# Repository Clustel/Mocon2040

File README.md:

# Mocon
A dev boards with an upgraded LDO compared to other traditional devboards, which will allow for using devices that need higher current draw. I made this to allow for easier prototyping as it gives extra breathing space when prototyping with many components connected at once to a dev board.

# Features
	RP2040 chip
	29 GPIO pins
	12Mhz Crystal
	High current LDO

# Schematic

# PCB	

# Ordering
Upload the zipped Prod folder to JLCPCB and go through their steps for a PCBA.

# BOM if u want to solder it on your own (might be more expensive than PCBA)
| Id | Designator | Footprint | Quantity | Comment |
| --- | --- | --- | --- | --- |
| 1 | C6,C12,C3,C17,C8,C5,C4,C7,C11,C2,C9 | C_0402_1005Metric | 11 | .1uF |
| 2 | C1,C10 | C_0402_1005Metric | 2 | 1uF |
| 3 | R7,R5 | C_0402_1005Metric | 2 | 1k |
| 4 | U2 | SOT-23-5 | 1 | AP2112K-3.3 |
| 5 | C13,C14 | C_0603_1608Metric | 2 | 10uF |
| 6 | C16,C15 | C_0402_1005Metric | 2 | 33pF |
| 7 | R2,R1 | C_0402_1005Metric | 2 | 5.1k |
| 8 | J1 | USB_C_Receptacle_HRO_TYPE-C-31-M-12 | 1 | USB_C_Receptacle_USB2.0_14P |
| 9 | SW1 | SW_Push_SPST_NO_Alps_SKRK | 1 | SW_Push |
| 10 | Y1 | Crystal_SMD_3225-4Pin_3.2x2.5mm | 1 | 12 MHz |
| 11 | R3,R4 | C_0402_1005Metric | 2 | 27 |
| 12 | U1 | QFN-56-1EP_7x7mm_P0.4mm_EP3.2x3.2mm | 1 | RP2040 |
| 13 | R6 | C_0402_1005Metric | 1 | 10k |
| 14 | J4 | PinHeader_1x03_P2.54mm_Vertical | 1 | Conn_01x03 |
| 15 | U3 | Winbond_USON-8-1EP_3x2mm_P0.5mm_EP0.2x1.6mm | 1 | W25Q16JVZPIQ TR |
| 16 | J2,J3 | PinHeader_1x20_P2.54mm_Vertical | 2 | Conn_01x20 |

# Silk Screen Sneak Peeks ;)

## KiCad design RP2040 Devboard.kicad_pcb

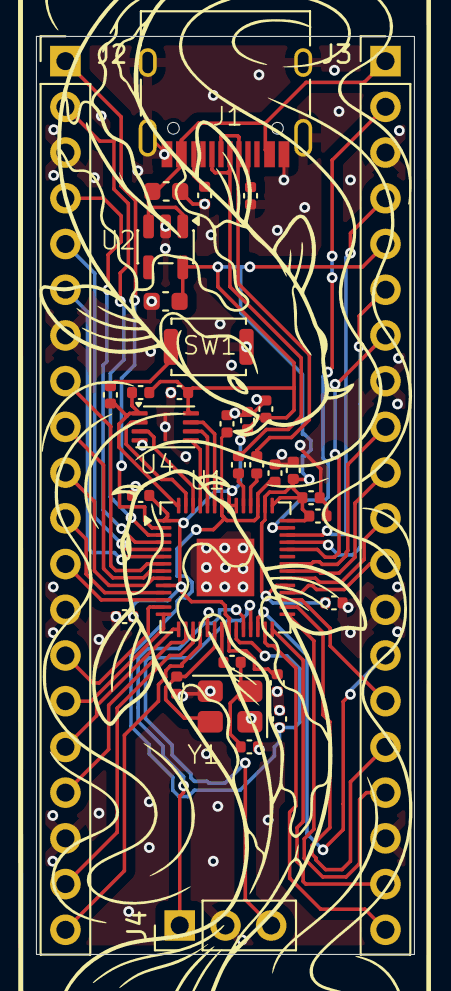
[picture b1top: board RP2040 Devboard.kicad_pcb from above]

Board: 2 copper layers, 21.0 x 51.0 mm, 33 parts (0 on the bottom side), 52 nets.

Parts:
C1, C10: 1uF; C_0402_1005Metric
C2, C3, C4, C5, C6, C7, C8, C9, C11, C12, C17: .1uF; C_0402_1005Metric
C13, C14: 10uF; C_0603_1608Metric
C15, C16: 33pF; C_0402_1005Metric
J1: USB_C_Receptacle_USB2.0_14P; USB_C_Receptacle_HRO_TYPE-C-31-M-12
J2, J3: Conn_01x20; PinHeader_1x20_P2.54mm_Vertical
J4: Conn_01x03; PinHeader_1x03_P2.54mm_Vertical
R1, R2: 5.1k; C_0402_1005Metric
R3, R4: 27; C_0402_1005Metric
R5, R7: 1k; C_0402_1005Metric
R6: 10k; C_0402_1005Metric
SW1: SW_Push; SW_Push_SPST_NO_Alps_SKRK
U1: RP2040; QFN-56-1EP_7x7mm_P0.4mm_EP3.2x3.2mm
U2: AP2112K-3.3; SOT-23-5
U3: W25Q16JVZPIQ TR; Winbond_USON-8-1EP_3x2mm_P0.5mm_EP0.2x1.6mm
Y1: 12 MHz; Crystal_SMD_3225-4Pin_3.2x2.5mm

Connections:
+1V1: C10.1, C11.1, C12.1, U1.23 (DVDD), U1.45 (VREG_VOUT), U1.50 (DVDD)
+3V3: C1.1, C2.1, C3.1, C4.1, C5.1, C6.1, C7.1, C8.1, C9.1, C13.1, C17.2, J3.5, R6.1, U1.1 (IOVDD), U1.10 (IOVDD), U1.22 (IOVDD), U1.33 (IOVDD), U1.42 (IOVDD), U1.43 (ADC_AVDD), U1.44 (VREG_VIN), U1.48 (USB_VDD), U1.49 (IOVDD), U2.5 (VOUT), U3.8 (VCC)
GND: C1.2, C2.2, C3.2, C4.2, C5.2, C6.2, C7.2, C8.2, C9.2, C10.2, C11.2, C12.2, C13.2, C14.2, C15.1, C16.1, C17.1, J1.A1 (GND), J1.A12 (GND), J1.B1 (GND), J1.B12 (GND), J1.S1 (SHIELD), J2.3, J2.7, J2.13, J2.18, J3.3, J3.8, J3.13, J3.18, J4.2, R1.2, R2.2, SW1.1, U1.19 (TESTEN), U1.57 (GND), U2.2 (GND), U3.4 (GND), U3.9 (EP), Y1.2 (G), Y1.4 (G)
GPIO0: J2.1, U1.2 (GPIO0)
GPIO1: J2.2, U1.3 (GPIO1)
GPIO2: J2.4, U1.4 (GPIO2)
GPIO3: J2.5, U1.5 (GPIO3)
GPIO4: J2.6, U1.6 (GPIO4)
GPIO5: J2.8, U1.7 (GPIO5)
GPIO6: J2.9, U1.8 (GPIO6)
GPIO7: J2.10, U1.9 (GPIO7)
GPIO8: J2.11, U1.11 (GPIO8)
GPIO9: J2.12, U1.12 (GPIO9)
GPIO10: J2.14, U1.13 (GPIO10)
GPIO11: J2.15, U1.14 (GPIO11)
GPIO12: J2.16, U1.15 (GPIO12)
GPIO13: J2.17, U1.16 (GPIO13)
GPIO14: J2.19, U1.17 (GPIO14)
GPIO15: J2.20, U1.18 (GPIO15)
GPIO16: J3.20, U1.27 (GPIO16)
GPIO17: J3.19, U1.28 (GPIO17)
GPIO18: J3.17, U1.29 (GPIO18)
GPIO19: J3.16, U1.30 (GPIO19)
GPIO20: J3.15, U1.31 (GPIO20)
GPIO21: J3.12, U1.32 (GPIO21)
GPIO22: J3.11, U1.34 (GPIO22)
GPIO23: J3.10, U1.35 (GPIO23)
GPIO24: J3.9, U1.36 (GPIO24)
GPIO26_ADC0: J3.7, U1.38 (GPIO26/ADC0)
GPIO27_ADC1: J3.6, U1.39 (GPIO27/ADC1)
GPIO28_ADC2: J3.4, U1.40 (GPIO28/ADC2)
GPIO29_ADC3: J3.2, U1.41 (GPIO29/ADC3)
unnamed: C16.2, R5.2, Y1.1
unnamed: J1.A5 (CC1), R1.1
unnamed: J1.B5 (CC2), R2.1
unnamed: R7.1, SW1.2
unnamed: R3.1, U1.46 (USB_DN)
unnamed: R4.1, U1.47 (USB_DP)
QSPI_SCLK: U1.52 (QSPI_SCLK), U3.6 (CLK)
QSPI_SD0: U1.53 (QSPI_SD0), U3.5 (DI/IO_{0})
QSPI_SD1: U1.55 (QSPI_SD1), U3.2 (DO/IO_{1})
QSPI_SD2: U1.54 (QSPI_SD2), U3.3 (~WP/IO_{2})
QSPI_SD3: U1.51 (QSPI_SD3), U3.7 (~HOLD/~RESET/IO_{3})
QSPI_SS: R6.2, R7.2, U1.56 (~QSPI_SS), U3.1 (~CS)
RUN: J3.14, U1.26 (RUN)
SWCLK: J4.1, U1.24 (SWCLK)
SWD: J4.3, U1.25 (SWDIO)
USB_DN: J1.A7 (D-), J1.B7 (D-), R3.2
USB_DP: J1.A6 (D+), J1.B6 (D+), R4.2
VBUS: C14.1, J1.A4 (VBUS), J1.A9 (VBUS), J1.B4 (VBUS), J1.B9 (VBUS), J3.1, U2.1 (VIN), U2.3 (EN)
XIN: C15.2, U1.20 (XIN), Y1.3
XOUT: R5.1, U1.21 (XOUT)

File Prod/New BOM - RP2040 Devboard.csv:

Id,Designator,Footprint,Quantity,Comment,Supplier and ref
1,"C6,C12,C3,C17,C8,C5,C4,C7,C11,C2,C9",C_0402_1005Metric,11,.1uF,
2,"C1,C10",C_0402_1005Metric,2,1uF,
3,"R7,R5",C_0402_1005Metric,2,1k,
4,U2,SOT-23-5,1,AP2112K-3.3,
5,"C13,C14",C_0603_1608Metric,2,10uF,
6,"C16,C15",C_0402_1005Metric,2,33pF,
7,"R2,R1",C_0402_1005Metric,2,5.1k,
8,J1,USB_C_Receptacle_HRO_TYPE-C-31-M-12,1,USB_C_Receptacle_USB2.0_14P,
9,SW1,SW_Push_SPST_NO_Alps_SKRK,1,SW_Push,
10,Y1,Crystal_SMD_3225-4Pin_3.2x2.5mm,1,12 MHz,
11,"R3,R4",C_0402_1005Metric,2,27,
12,U1,QFN-56-1EP_7x7mm_P0.4mm_EP3.2x3.2mm,1,RP2040,
13,R6,C_0402_1005Metric,1,10k,
14,J4,PinHeader_1x03_P2.54mm_Vertical,1,Conn_01x03,
15,U3,Winbond_USON-8-1EP_3x2mm_P0.5mm_EP0.2x1.6mm,1,W25Q16JVZPIQ TR,
16,"J2,J3",PinHeader_1x20_P2.54mm_Vertical,2,Conn_01x20,

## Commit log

2026-05-15 Github cleanup
